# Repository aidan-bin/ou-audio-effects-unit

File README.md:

# STM32 Audio Effects Unit

STM32 audio effects project with fixed-point DSP in C, STM32 firmware, a Python demo UI, and hardware design files.

## Repository Layout

- [dsp](dsp): portable DSP and math code
- [firmware](firmware): STM32 target firmware
    - [custom board firmware](firmware/stm32f303/cubemx): CubeMX project for custom board
    - [nucleo firmware](firmware/stm32f303/nucleo-ou-audio-effects): CubeMX project for Nucleo F303RE
- [host](host): host-side demo tooling and HIL CLI tools
- [hardware](hardware): board and analog design assets
- [tests](tests): test assets
- [docs](docs): setup, architecture, bring-up notes
- [scripts](scripts): helper scripts

## Quick Start: Host Demo

```sh
./scripts/run.sh demo
```

Builds the DSP library, prepares a local demo virtualenv, installs demo deps, and starts the UI.

## Firmware

The STM32 firmware source code is generated locally with CubeMX and is not checked into this repository. There are two CubeMX projects: one for the custom board and one for the Nucleo F303RE. These projects use the same DSP and application code, but with separate configurations.

- FreeRTOS task-based control flow
- DMA-driven ADC/DAC audio transfer
- ping-pong sample buffering
- effect model/state/control and processing tasks
- I2C path for peripherals (EEPROM/display)
- CLI for configuration and logging over USART

## Tests

```sh
./scripts/run.sh
```

Default check flow (preflight + build + tests).

Full gate (format + lint + build + tests):

```sh
./scripts/run.sh check-full
```

Tests only:

```sh
./scripts/run.sh test
```

Build-only commands:

```sh
./scripts/run.sh build
./scripts/run.sh build-tests
./scripts/run.sh build-firmware
./scripts/run.sh build-demo
```

- `build`: builds host test targets plus firmware for both custom board and Nucleo projects
- `build-tests`: builds host test targets only
- `build-firmware`: builds firmware for both custom board and Nucleo projects
- `build-demo`: builds only the shared DSP library for the Python demo

Format check only:

```sh
./scripts/run.sh format-check
```

Formatting/linting will skip CubeMX-generated code regions.

Clean artifacts:

```sh
./scripts/run.sh clean
```

Dependency check:

```sh
./scripts/run.sh doctor
```

## Hardware

Board assets are under [hardware/STM32AudioEffects](hardware/STM32AudioEffects), with analog simulation files under [hardware/LTspice](hardware/LTspice).

## Live Demo

```sh
python host/python-cli/live_mic_effects.py
```

Streams your microphone through the effects pipeline in realtime over USB and plays the result through your speakers.

Keybindings:

| Key | Action |
|-----|--------|
| `1` `2` `3` | Switch active effect (overdrive / echo / compression) |
| `↑` `↓`    | Adjust primary parameter of active effect |
| `e`         | Toggle active effect on/off |
| `i`         | Print current params |
| `s`         | Print sysinfo |
| `q`         | Quit |

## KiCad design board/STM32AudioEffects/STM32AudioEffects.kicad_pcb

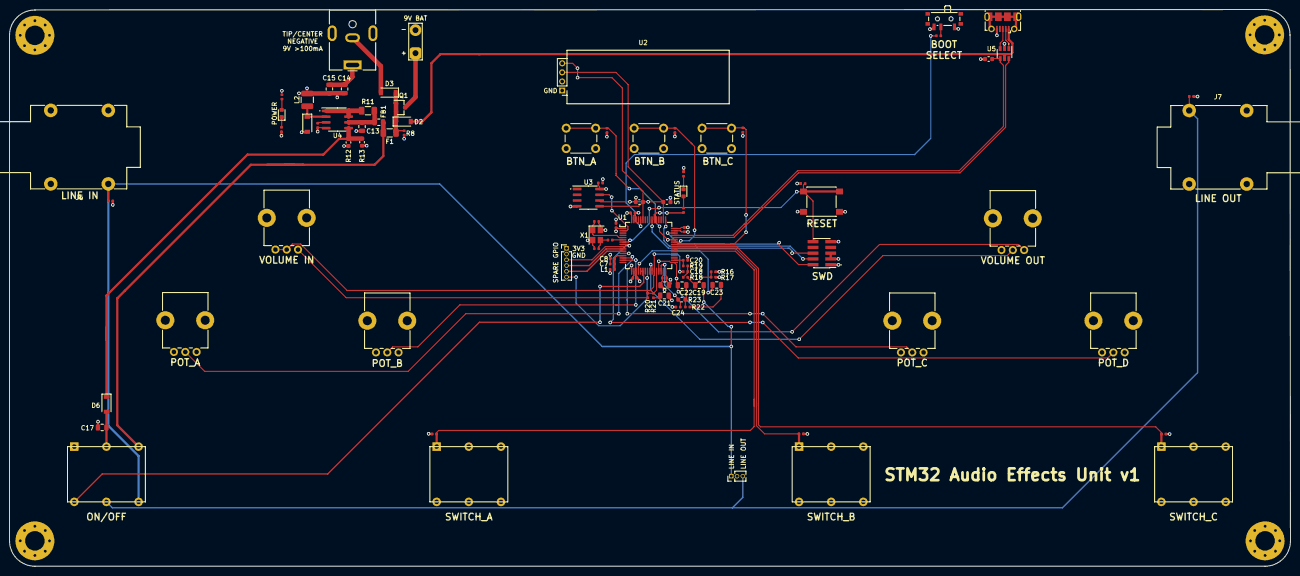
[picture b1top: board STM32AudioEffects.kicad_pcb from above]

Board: 4 copper layers, 282.8 x 122.9 mm, 97 parts (0 on the bottom side), 65 nets.

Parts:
BT1: 9V; TestPoint_2Pads_Pitch5.08mm_Drill1.3mm
C1, C13: 4.7u; C_0805_2012Metric
C2, C3, C4, C5, C6, C11, C12: 100n; C_0402_1005Metric
C7: 1u; C_0402_1005Metric
C8: 10n; C_0402_1005Metric
C9, C10: 33p; C_0402_1005Metric
C14: 22u; C_0805_2012Metric
C15, C17, C19, C21, C23: 10u; C_0805_2012Metric
C16: 330p; C_0402_1005Metric
C18, C20, C24: 1n; C_0402_1005Metric
C22: 2.2n; C_0805_2012Metric
D1: BLUE; LED_0603_1608Metric
D2, D3, D5, D6: B5819W; D_SOD-123
D4: GREEN; LED_0603_1608Metric
F1: 250mA; Fuse_1206_3216Metric
FB1: 600@600MHz; L_0805_2012Metric
H1, H2, H3, H4: MountingHole_Pad; MountingHole_4.3mm_M4_Pad_Via
J1: Barrel_Jack; BarrelJack_CUI_PJ-063AH_Horizontal
J2: SWD; PinHeader_2x05_P1.27mm_Vertical_SMD
J3: Conn_01x03; PinHeader_1x03_P1.27mm_Vertical
J4: USB_B_Micro; USB_Micro-B_Molex-105017-0001
J5: Conn_01x06; PinHeader_1x06_P1.27mm_Vertical
J6, J7: 6.35mm Jack; Jack_6.35mm_Neutrik_NMJ4HFD2_Horizontal
L1: 39n; L_0402_1005Metric
L2: 220u; L_1210_3225Metric
Q1: AO3401A; SOT-23
R1: 220; R_0402_1005Metric
R2, R8, R24, R25, R26, R27, R28, R29: 10k; R_0402_1005Metric
R3: 1.5k; R_0603_1608Metric
R4, R7: 4.7k; R_0603_1608Metric
R5, R9: 0; R_0402_1005Metric
R6, R10: 33; R_0402_1005Metric
R11: 2; R_1206_3216Metric
R12: 18k; R_0603_1608Metric
R13: 11k; R_0603_1608Metric
R14, R15: 1M; R_0402_1005Metric
R16, R17: 220k; R_0402_1005Metric
R18: 1.2k; R_0402_1005Metric
R19: 24k; R_0402_1005Metric
R20: 27k; R_0402_1005Metric
R21: 2.4k; R_0402_1005Metric
R22: 3.3k; R_0402_1005Metric
R23: 4.3k; R_0603_1608Metric
RV1, RV2, RV3, RV4, RV5, RV6: 10k; Potentiometer_Alps_RK09K_Single_Vertical
SW1: SW_Push; SW_SPST_PTS645
SW2: SW_SPDT; SW_SPDT_PCM12
SW3: SW_PUSH_OFF_ON_DPDT; SW_DPDT_FOOT_17.2x12.2mm_Vertical
SW4, SW5, SW6: OFF_MOM; SW_PUSH_6mm_H13mm
SW7, SW8, SW9: SW_SPST; SW_DPDT_FOOT_17.2x12.2mm_Vertical
U1: STM32F303RETx; LQFP-64_10x10mm_P0.5mm
U2: I2C_OLED_Display; I2C_OLED_DISPLAY
U3: M24C64; SOIC-8_3.9x4.9mm_P1.27mm
U4: MC34063AD; SOIC-8_3.9x4.9mm_P1.27mm
U5: USBLC6-2SC6; SOT-23-6
X1: 12MHz; Crystal_SMD_3225-4Pin_3.2x2.5mm

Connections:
+3.3VA: C7.1, C8.2, L1.2, U1.13
+3V3: C1.1, C2.2, C3.2, C4.2, C5.2, C6.2, C12.2, C14.1, C15.1, J2.1, J5.1, L1.1, L2.2, R3.1, R4.1, R7.1, R9.1, R12.2, R17.1, RV3.1, RV4.1, RV5.1, RV6.1, SW2.3, SW4.2, SW5.2, SW6.2, SW7.2, SW8.2, SW9.2, U1.1, U1.19, U1.32, U1.48, U1.64, U2.3, U3.8
/LED_STATUS: D1.2, R5.2
/audio i/o/IN_OPAMP_BIAS: C19.1, R16.1, R17.2, R18.2
/power/1.25V: D6.1, R12.1, R13.1, U4.5
BOOT0: R2.1, U1.60
BTN_A: R24.2, SW4.1, U1.43
BTN_B: R25.2, SW5.1, U1.42
BTN_C: R26.2, SW6.1, U1.41
BUCK_IN: F1.1, FB1.2, SW3.3
DAC1_OUT1: C23.2, U1.20
GND: BT1.2, C1.2, C2.1, C3.1, C4.1, C5.1, C6.1, C7.2, C8.1, C9.2, C10.2, C11.2, C12.1, C13.2, C14.2, C15.2, C16.1, C17.2, C20.1, C21.2, C24.1, D5.2, H1.1, H2.1, H3.1, H4.1, J1.1, J2.3, J2.5, J2.9, J3.2, J4.5, J5.2, J6.S, J7.S, R6.2, R8.2, R10.2, R13.2, R14.2, R15.2, R16.2, R24.1, R25.1, R26.1, R27.1, R28.1, R29.1, RV2.3, RV3.3, RV4.3, RV5.3, RV6.3, SW1.1, SW2.1, SW3.1, U1.12, U1.18, U1.31, U1.47, U1.63, U2.4, U3.4, U4.4, U5.2, X1.2, X1.4
HSE_IN: C9.1, U1.5, X1.1
HSE_OUT: R1.1, U1.6
I2C1_SCL: R4.2, U1.50, U2.2, U3.6
I2C1_SDA: R7.2, U1.59, U2.1, U3.5
LINE_IN: C19.2, J3.1, J6.T, R14.1, SW3.6
LINE_OUT: J3.3, J7.T, R15.1, SW3.5
NRST: C11.1, J2.10, SW1.2, U1.7
unnamed: BT1.1, Q1.3
unnamed: C10.1, R1.2, X1.3
unnamed: C13.1, FB1.1, R11.1, U4.6
unnamed: C16.2, U4.3
unnamed: C17.1, D6.2, SW3.2
unnamed: C18.1, R18.1, R19.2
unnamed: C21.1, R21.1
unnamed: C22.1, R22.1, R23.2
unnamed: C23.1, R22.2
unnamed: D1.1, R6.1
unnamed: D2.1, D3.1, F1.2, Q1.1, Q1.2, R8.1
unnamed: D3.2, J1.2
unnamed: D4.1, R10.1
unnamed: D4.2, R9.2
unnamed: D5.1, L2.1, U4.2
unnamed: R2.2, SW2.2
unnamed: R5.1, U1.54
unnamed: R11.2, U4.1, U4.7, U4.8
unnamed: R20.2, RV1.1
OPAMP2_VIN+: RV2.2, U1.26
OPAMP2_VIN-: SW3.4, U1.21, U1.22
OPAMP3_VIN+: C20.2, R19.1, U1.34
OPAMP3_VIN-: R20.1, R21.2, U1.28
OPAMP3_VOUT: C18.2, RV1.2, RV1.3, U1.27
OPAMP4_VIN+: C24.2, R23.1, U1.30
OPAMP4_VIN-: C22.2, RV2.1, U1.29, U1.33
PC1: J5.3, U1.9
PC2: J5.4, U1.10
PC3: J5.5, U1.11
PC4: J5.6, U1.24
POT_A: RV3.2, U1.14
POT_B: RV4.2, U1.15
POT_C: RV5.2, U1.17
POT_D: RV6.2, U1.8
SWDCLK: J2.4, U1.49
SWDIO: J2.2, U1.46
SWITCH_A: R27.2, SW7.1, U1.38
SWITCH_B: R28.2, SW8.1, U1.39
SWITCH_C: R29.2, SW9.1, U1.40
SWO: J2.6, U1.55
USB_CONN_D+: J4.3, U5.3
USB_CONN_D-: J4.2, U5.1
USB_D+: R3.2, U1.45, U5.4
USB_D-: U1.44, U5.6
VBUS: D2.2, J4.1, U5.5
~NVM_WE: U1.2, U3.7

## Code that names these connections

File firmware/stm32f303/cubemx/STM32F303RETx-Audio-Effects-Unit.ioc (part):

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Mcu.Name=STM32F303R(D-E)Tx
Mcu.Package=LQFP64
Mcu.UserName=STM32F303RETx
PA0.GPIOParameters=GPIO_Label
PA0.GPIO_Label=POT_A
PA0.Mode=IN1-Single-Ended
PA0.Signal=ADC1_IN1
PA1.GPIOParameters=GPIO_Label
PA1.GPIO_Label=POT_B
PA1.Mode=IN2-Single-Ended
PA1.Signal=ADC1_IN2
PA10.GPIOParameters=GPIO_Label
PA10.GPIO_Label=BTN_A
PA10.Signal=GPXTI10
PA11.Mode=Device
PA11.Signal=USB_DM
PA12.Mode=Device
PA12.Signal=USB_DP
PA13.Mode=Trace_Asynchronous_SW
PA13.Signal=SYS_JTMS-SWDIO
PA14.Mode=Trace_Asynchronous_SW
PA14.Signal=SYS_JTCK-SWCLK
PA15.GPIOParameters=GPIO_Pu
PA15.GPIO_Pu=GPIO_PULLUP
PA15.Mode=I2C
PA15.Signal=I2C1_SCL
PA3.GPIOParameters=GPIO_Label
PA3.GPIO_Label=POT_C
PA3.Mode=IN4-Single-Ended
PA3.Signal=ADC1_IN4
PA4.Signal=COMP_DAC11_group
PA5.Mode=Standalone
PA5.Signal=OPAMP2_VINM
PA6.Mode=Standalone
PA6.Signal=OPAMP2_VOUT
PA8.GPIOParameters=GPIO_Label
PA8.GPIO_Label=BTN_C
PA8.Signal=GPXTI8
PA9.GPIOParameters=GPIO_Label
PA9.GPIO_Label=BTN_B
PA9.Signal=GPXTI9
PB0.Mode=Standalone
PB0.Signal=OPAMP2_VINP
PB1.Mode=Standalone
PB1.Signal=OPAMP3_VOUT
PB10.Mode=Standalone
PB10.Signal=OPAMP4_VINM
PB11.Mode=Standalone
PB11.Signal=OPAMP4_VINP
PB12.Mode=Standalone
PB12.Signal=OPAMP4_VOUT
PB13.Mode=Standalone
PB13.Signal=OPAMP3_VINP
PB2.Mode=Standalone
PB2.Signal=OPAMP3_VINM
PB3.Mode=Trace_Asynchronous_SW
PB3.Signal=SYS_JTDO-TRACESWO
PB7.GPIOParameters=GPIO_Pu
PB7.GPIO_Pu=GPIO_PULLUP
PB7.Mode=I2C
PB7.Signal=I2C1_SDA
PC0.GPIOParameters=GPIO_Label
PC0.GPIO_Label=POT_D
PC0.Signal=ADCx_IN6
PC13.GPIOParameters=PinState,GPIO_Label
PC13.GPIO_Label=nNVM_WE
PC13.PinState=GPIO_PIN_SET
PC13.Signal=GPIO_Output
PC6.GPIOParameters=GPIO_Label
PC6.GPIO_Label=STATUS_LED
PC6.Signal=GPIO_Output
PC7.GPIOParameters=GPIO_Label
PC7.GPIO_Label=SWITCH_A
PC7.Signal=GPIO_Input
PC8.GPIOParameters=GPIO_Label
PC8.GPIO_Label=SWITCH_B
PC8.Signal=GPIO_Input
PC9.GPIOParameters=GPIO_Label
PC9.GPIO_Label=SWITCH_C
PC9.Signal=GPIO_Input
PD2.GPIOParameters=GPIO_Label
PD2.GPIO_Label=LED_STATUS
PD2.Signal=GPIO_Output
PF0-OSC_IN.GPIOParameters=GPIO_Label
PF0-OSC_IN.GPIO_Label=HSE_IN
PF0-OSC_IN.Mode=HSE-External-Oscillator
PF0-OSC_IN.Signal=RCC_OSC_IN
PF1-OSC_OUT.GPIOParameters=GPIO_Label
PF1-OSC_OUT.GPIO_Label=HSE_OUT
PF1-OSC_OUT.Mode=HSE-External-Oscillator
PF1-OSC_OUT.Signal=RCC_OSC_OUT
RCC.HSE_VALUE=12000000
RCC.SYSCLKFreq_VALUE=48000000
RCC.SYSCLKSourceVirtual=RCC_SYSCLKSOURCE_PLLCLK
board=custom

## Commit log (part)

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2026-05-25 chore: v0
2026-05-26 Restructure repository layout and rewrite README
2026-05-26 Trim README for developer-first audience
2026-05-26 Further condense README
2026-05-26 Add setup, architecture, and bring-up docs
2026-05-26 Add CMake and core tooling baseline
2026-05-26 Add deterministic DSP test baseline
2026-05-26 Add GitHub Actions CI workflow
2026-05-26 Clean up fast math constants
2026-05-26 Reduce DSP lint noise
2026-05-26 Remove obsolete effects testbench
2026-05-26 Make host demo path-independent
2026-05-26 Add unified check script
2026-05-26 Sync setup docs with current host loader
2026-05-26 Add clean script for generated artifacts
2026-05-26 Harden echo edge-case handling
2026-05-26 Tidy effect core internals
2026-05-26 Tune lint policy for legacy API noise
2026-05-26 Clean up lint script output
2026-05-26 Fix docs link integrity
2026-05-26 Add format-check and normalize DSP style
2026-05-26 Add high-density echo regression test
2026-05-26 Expand overdrive regression coverage
2026-05-26 Add DSP edge-case regression tests
2026-05-26 Clamp out-of-range DSP params
2026-05-26 Add echo pre-delay boundary regression
2026-05-26 Use platform-native shared library suffix
2026-05-26 Remove legacy moving-averager code
2026-05-26 Saturate echo mix to uint16 range
2026-05-26 Normalize echo controls to documented bounds
2026-05-26 Add zero-delay echo regression
2026-05-26 Auto-detect versioned clang tools in scripts
2026-05-26 Add echo decay clamp regression
2026-05-26 Add overdrive clamp regression tests
2026-05-26 Remove redundant build in check workflow
2026-05-26 Skip redundant configure in lint script
2026-05-26 Add doctor script for dependency checks
2026-05-26 Reconfigure tests when build type drifts
2026-05-26 Make CI tooling dependencies explicit
2026-05-26 Improve doctor portability checks
2026-05-26 Configure lint cache as Release
2026-05-26 Run doctor at start of full checks
2026-05-26 Run doctor in standard check flow
2026-05-26 Avoid duplicate doctor runs in full checks
2026-05-26 Document doctor preflight in check scripts
2026-05-26 Refactor fixed-point clamping helpers in effects
2026-05-26 Add q_tanh odd-symmetry regression
2026-05-26 Add compression sign-symmetry regression
2026-05-26 Add robust q_tanh shape regressions
2026-05-26 Refactor versioned tool checks in doctor
2026-05-26 Remove stale commented code in fast_math
2026-05-26 Centralize versioned tool resolution in scripts
2026-05-26 Share DSP file list across format scripts
2026-05-26 Share Release build-tree guard across scripts
2026-05-26 Add echo attack monotonic regression
2026-05-27 Add effect runtime abstraction layer
2026-05-27 Clean up Python host runtime wiring
2026-05-27 Simplify Python host bindings
2026-05-27 Refactor Python signal building
2026-05-27 Consolidate Python effect application
2026-05-27 Simplify Python effect flow
2026-05-27 Fix Python signal merge resize error
2026-05-27 Remove lambda wrappers in Python effects
2026-05-27 Wire firmware effects through runtime slots
2026-05-27 Add effect handle regression tests
2026-05-27 Harden firmware echo delay handling
2026-05-27 Expand echo delay accessor guard tests
2026-05-27 Atomically latch effects state and params
2026-05-27 Unify effects-loop failure cleanup path
2026-05-27 Harden switch and pot effect index handling
2026-05-27 Fix ROM payload handling and DAC copy guard
2026-05-27 Harden i2c message validation and failure signaling
2026-05-27 Avoid ROM transmit payload double-free after enqueue
2026-05-29 Normalize effects state flow and consolidate ADC mapping
2026-05-29 Harden DMA waits and ISR wakeup scheduling
2026-05-30 Consolidate I2C ROM handoff paths
2026-05-30 Harden math helpers for signed conversion and overflow
2026-05-30 Add zero-delay echo normalization regression
2026-05-30 Move BAM helpers into DSP tests
2026-05-31 Extract firmware state/control logic into testable app modules
2026-05-31 Add host peripheral mock framework and tests
2026-06-01 Extract pipeline/I2C/ROM modules with host tests and CMake build
2026-06-01 Extract peripheral dispatch and add host callback tests
2026-06-01 Move I2C/ROM support initialization into app modules
2026-06-01 Extract effects task step and add host tests
2026-06-01 Extract pot task step and add host tests
2026-06-01 Extract switch task step and add host tests
2026-06-01 Clarify ROM write-disable polarity semantics
2026-06-01 Remove display command queue; fix I2CMessage → I2CHandlerMessage in CubeMX
2026-06-01 Add HT6 task integration test and CMake target
2026-06-01 Unify firmware effects model includes
2026-06-01 Document merged firmware effects model
2026-06-01 Adopt shared assertion helper in host tests
2026-06-01 Expand shared host test assertions
2026-06-01 Finish shared assertion helper migration
2026-06-01 Remove compatibility header shims
2026-06-01 Consolidate scripts
2026-06-01 Cleanup CMake files
2026-06-02 Refine docs
2026-06-02 Cleanup comments and formatting
2026-06-03 Update gitignore
2026-06-04 Setup lint/format flow
2026-06-04 Mass format pass
2026-06-04 Add CLI layer
2026-06-05 Add USB device, fix format/lint missing files
2026-06-07 Add on-target testing/logging, add Nucleo code to format/lint
2026-06-07 Enhance CLI logging
2026-06-07 Cleanup CLI code
2026-06-07 Refine buffering logic
2026-06-07 Add GH release workflow (to be verified)
2026-06-08 Add stats log, panic logs, fix STATUS_LED actually being B1, fix DMA config not set to continuous
2026-06-08 Add output test vector support, add sweep vector
2026-06-08 Add bypass handling
2026-06-08 Add CLI reference
2026-06-08 Cleanup magic numbers
2026-06-08 Cleanup CLI adapter
2026-06-09 Add reboot command
2026-06-09 Use B1 to toggle test mode
2026-06-09 Add info command
2026-06-09 Fix test
2026-06-18 Fix workflow
2026-06-22 Remove frequency limit for CLI
2026-06-22 Fix sweep magnitude at high frequencies
2026-06-24 Bringup I2C for Nucleo, add fault handler, move failures to STATUS_LED
2026-06-25 Eliminate redundant echo buf
2026-06-25 Enable USB peripheral
2026-06-25 Update Nucleo output schematic
2026-06-27 Add new vectors (including .wav conversion), add USB audio stream prototype, make log stream interactive only
2026-06-27 Implement Python style guide
2026-06-27 Lint pass
2026-06-28 Table-drive test-vector name<->id in cli_core
    Replace test_vector_name if-chain and the 6-way vector parse with one
    TEST_VECTORS table + test_vector_id lookup. Same names/ids/fallback. -27 LoC.
2026-06-28 Extract write_byte_list and parse_u32_max helpers in cli_core
    Collapse the three identical i2c hex-dump blocks (scan/read/recv) into one
    write_byte_list helper, and fold the repeated 'parse u32 + bound' checks into
    parse_u32_max. Identical output and validation. -28 LoC, lower branching.
2026-06-28 Reuse finish_message for i2c invalid-message cleanup
    The invalid-message branch inlined finish_message's exact cleanup (set failed,
    free payload, signal completion). Call finish_message instead. -15 LoC.
2026-06-28 Refactor fault_handler reason dumps to bit tables
    Replace three repetitive if-chains (usage/bus/mem CFSR + HFSR bits) with
    {mask,text} tables walked by a shared dump_reason_bits helper. Output strings
    and order are unchanged; BFAR/MMFAR special prints retained. -21 LoC.
2026-06-28 Table-drive effects_model pot-to-parameter mapping
    Replace the nested switch(effect)->switch(pot) (CC ~13) with an offset-based
    POT_MAP[effect][pot] table and a single assign path. Preserves the no-op-true
    behavior for compression pots 2/3 and false for out-of-range pots/effects.
2026-06-28 Merge duplicate compile-db resolvers in workflows.sh
    resolve_cubemx/nucleo_compile_db_dir differed only by env-var name and project
    dir. Merge into resolve_generated_compile_db_dir(env_var, project_dir) using
    ${!var} indirection. Behavior verified equivalent (fallback/override/error).
2026-06-28 Refactor cli_service_adapter config/state maps to tables
    Replace four mirrored strcmp chains (set/get param, set/get state) with
    offset-based lookup tables. Behavior is identical: same keys, bounds, and
    INT32_MAX overflow guard. -43 LoC, much lower branching.
2026-06-28 Simplify drain_semaphore ops initializer
    Use a designated initializer for the single non-NULL field; the rest are
    zero-initialized as before. -12 LoC.
2026-06-28 Simplify peripheral_dispatch guards and I2C hooks
    Add REQUIRE_OPS guard macro for the ISR notify hooks, and route the four
    near-identical I2C completion hooks through one peripheral_signal_i2c helper
    (error flag + optional log message). Behavior identical.
2026-06-28 Fix stale references in docs and demo loader
    - effects.py pointed users at ./scripts/build.sh (does not exist); the real
    command is ./scripts/run.sh build-demo.
    - README Live Demo section documented host/python-cli/live_mic_effects.py,
    which is not in the repo; remove it and the 'HIL CLI tools' layout claim.
    Re-add if that tool lands.
2026-06-28 Extract scale_sample and phase_step_q16 helpers in test_vector_source
    Fold the repeated 'scale by amplitude + center on X_AXIS + saturate' into
    scale_sample (4 sites) and the LUT phase-increment math into phase_step_q16.
    Identical arithmetic; tests unchanged.
2026-06-28 Use implicit f-string concatenation in effects.py __str__
    Drop redundant + operators between adjacent f-string literals. No behavior
    change.
2026-06-28 Deduplicate clamp helpers into fast_math
    clamp_range/clamp_qn/clamp_min were defined identically in effects.c and
    effect_runtime.c. Move the single definition into the fast_math math module
    and include it from both. Identical semantics; DSP tests unchanged. -~40 LoC.
2026-06-28 Generate USB other-speed descriptor from FS descriptor
    The other-speed config descriptor was a 135-line byte-for-byte copy of the FS
    descriptor differing only in the descriptor-type field. Replace the literal
    with an on-demand memcpy+patch in GetOtherSpeedCfgDesc. Emitted bytes are
    identical. Firmware-only file (untested on host); isolated commit for bisect.
2026-06-28 Format/lint pass, cleanup comments
2026-06-28 Simplify usbd_cdc_dual instance dispatch
    - CLASS setup: hoist cmd op-code/length pointers via ternary instead of
    branching on inst.
    - EP0_RxReady: factor dispatch_pending_control() called for each instance.
    - Route public Rx/Tx buffer setters through set_rx_buffer/set_tx_buffer.
2026-06-28 Simplify DSP: delegate clamp_min, hoist overdrive invariant, compound-literal defaults
2026-06-28 test_dsp: adopt shared harness + EXPECT_OK macro
    Add expect_eq_i16, expect_eq_u16_array, and an EXPECT_OK early-return macro to
    the shared harness; drop test_dsp's local duplicates and collapse 29 copy-pasted
    !=0 error-check blocks into EXPECT_OK calls. -176 LoC in test_dsp.
2026-06-28 test_firmware_effects_task: extract make_task_context + set_overdrive_params helpers
2026-06-28 test_firmware_cli_service_adapter: extract setup_adapter fixture for NULL-ops tests
2026-06-28 Reuse write_byte_list for rom-read hex dump in cli_core
2026-06-28 test_dsp: table-drive the 5 overdrive param-clamp parity tests
2026-06-28 Remove dead fields: TestVectorSource.wav_index, UsbAudioStream.input_active
2026-06-28 test_firmware_cli_core: extract reset_output() helper (20 call sites)
2026-06-29 Refine USB stream, remove echo allocations
2026-06-29 Minor cleanup
2026-06-29 Improve QN portability, refine QN math
2026-06-29 Support arbitrary effects number
2026-06-29 Support re-ordering effects
2026-06-29 Format/lint pass
